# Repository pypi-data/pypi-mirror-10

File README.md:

# PyPI code 10

This repository is part of a project to make all code in PyPI as accessible as possible. For more information 
on the project and to find out how to utilise this data, see the website: https://py-code.org/

This repo contains 40000 packages uploaded to PyPI between 
2015-04-15 19:18 and 2015-07-14 03:23.

The repo is 99% (39941/40000) complete.

Package contents can be found [in the code branch](https://github.com/pypi-data/pypi-mirror-10/tree/code/packages).

A browsable package list for all repositories [all packages here](https://py-code.org/repositories/pypi-mirror-10).

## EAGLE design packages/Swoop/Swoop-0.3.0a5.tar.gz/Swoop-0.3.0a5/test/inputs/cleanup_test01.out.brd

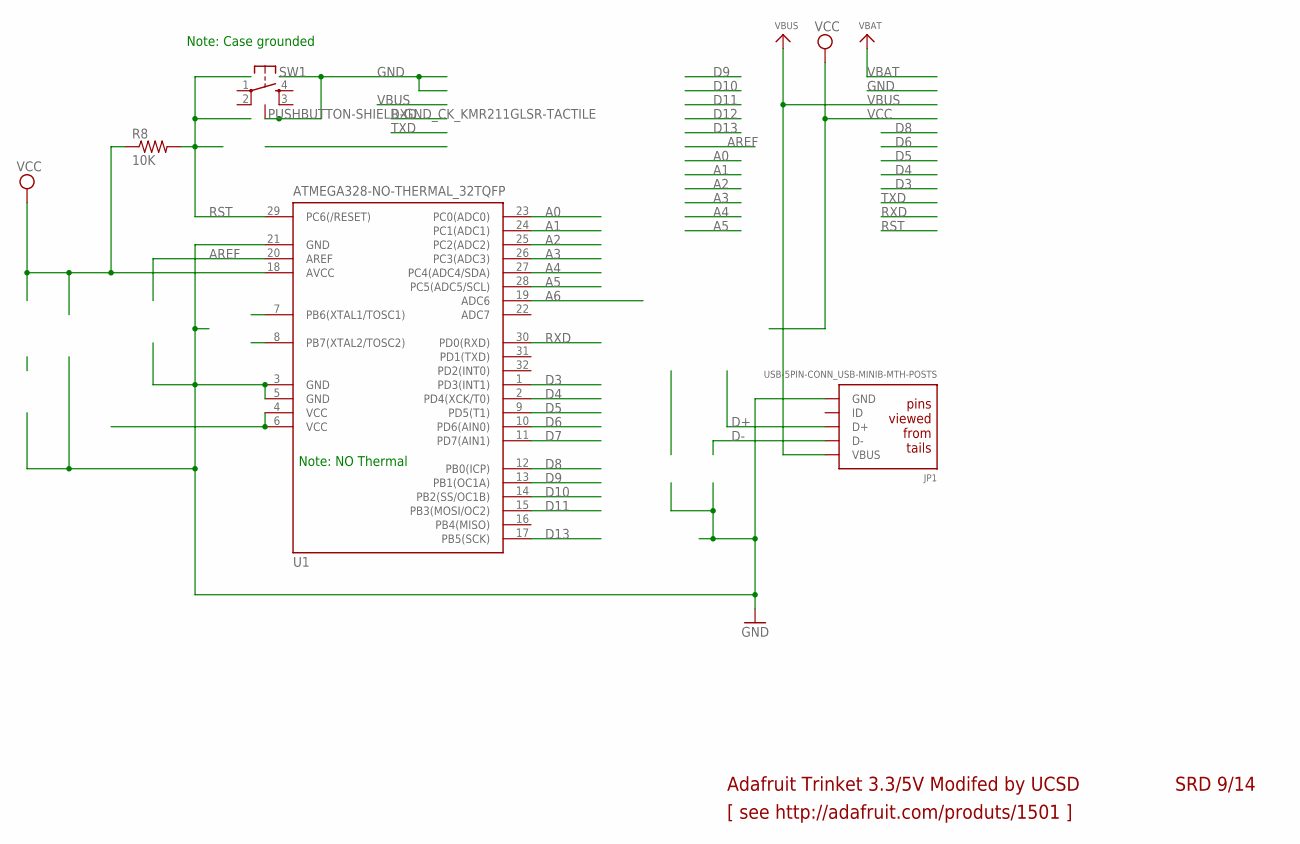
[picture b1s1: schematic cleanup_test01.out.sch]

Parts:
JP1: USB-5PIN-CONN_USB-MINIB-MTH-POSTS; FCI_10033526; MPN 10033526-N3212MLF
SW1: PUSHBUTTON-SHIELD-GND_CK_KMR211GLSR-TACTILE; CK_KMR211GLSR; MPN KMR211GLFS
U1: ATMEGA328-NO-THERMAL_32TQFP; QFP80P900X900X120-32L30HS; MPN ATMEGA328-AU

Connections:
A0: U1.23 (PC0(ADC0))
A1: U1.24 (PC1(ADC1))
A2: U1.25 (PC2(ADC2))
A3: U1.26 (PC3(ADC3))
A4: U1.27 (PC4(ADC4/SDA))
A5: U1.28 (PC5(ADC5/SCL))
A6: U1.19 (ADC6)
AREF: U1.20 (AREF)
D3: U1.1 (PD3(INT1))
D4: U1.2 (PD4(XCK/T0))
D5: U1.9 (PD5(T1))
D6: U1.10 (PD6(AIN0))
D7: U1.11 (PD7(AIN1))
D8: U1.12 (PB0(ICP))
D9: U1.13 (PB1(OC1A))
D10: U1.14 (PB2(SS/OC1B))
D11: U1.15 (PB3(MOSI/OC2))
D13: U1.17 (PB5(SCK))
D+: JP1.3 (D+)
D-: JP1.2 (D-)
GND: JP1.5 (GND), SW1.1, SW1.4, SW1.5, U1.3 (GND), U1.5 (GND), U1.21 (GND)
unnamed: U1.4 (VCC), U1.6 (VCC)
RST: SW1.2, SW1.3, U1.29 (PC6(/RESET))
RXD: U1.30 (PD0(RXD))
VBUS: JP1.1 (VBUS)
VCC: U1.18 (AVCC)

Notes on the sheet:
[ see http://adafruit.com/produts/1501 ]
Adafruit Trinket 3.3/5V Modifed by UCSD
SRD 9/14
Note: Case grounded
Note: NO Thermal

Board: 2 copper layers, 3 parts (0 on the bottom side), 3 nets, no tracks yet.

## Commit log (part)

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2023-08-06 Add package airship-icloud/1.4.6/airship_icloud-1.4.6-py2.py3-none-any.whl
2023-08-06 Add package fontaine/1.3.2/fontaine-1.3.2.tar.gz
2023-08-06 Add package coala/0.1.1.dev1694/coala-0.1.1.dev1694.tar.gz
2023-08-06 Add package phconvert/0.6.2/phconvert-0.6.2-py2.py3-none-any.whl
2023-08-06 Add package coala/0.1.1.dev1695/coala-0.1.1.dev1695.tar.gz
2023-08-06 Add package planetary_test_data/0.3.0/planetary_test_data-0.3.0.tar.gz
2023-08-06 Add package django-post-office/2.0.0/django-post_office-2.0.0.tar.gz
2023-08-06 Add package PySMT/0.4.1/PySMT-0.4.1.tar.gz
2023-08-06 Add package processout/1.2.0/processout-1.2.0.tar.gz
2023-08-06 Add package ipaddress/1.0.11/ipaddress-1.0.11-py27-none-any.whl
2023-08-06 Add package ftw.testbrowser/1.16.1/ftw.testbrowser-1.16.1.tar.gz
2023-08-06 Add package ipaddress/1.0.11/ipaddress-1.0.11.tar.gz
2023-08-06 Add package jmbo-sitemap/2.0.1/jmbo-sitemap-2.0.1.tar.gz
2023-08-06 Add package pyTelegramBotAPI/0.2.3/pyTelegramBotAPI-0.2.3.tar.gz
2023-08-06 Add package gocardless-pro/0.1.2/gocardless_pro-0.1.2.tar.gz
2023-08-06 Add package muffin/0.0.95/muffin-0.0.95-py2.py3-none-any.whl
2023-08-06 Add package pytest-splinter/1.4.6/pytest-splinter-1.4.6.tar.gz
2023-08-06 Add package frojd-fabric/1.1.1/frojd-fabric-1.1.1.tar.gz
2023-08-06 Add package aTXT/1.0.5.7/aTXT-1.0.5.7.tar.gz
2023-08-06 Add package pyshark/0.3.6/pyshark-0.3.6.tar.gz
2023-08-06 Add package consular/0.1.0/consular-0.1.0.tar.gz
2023-08-06 Add package git-gifi/0.5/git_gifi-0.5-py2.7.egg
2023-08-06 Add package django-reversion-compare/0.5.3/django_reversion_compare-0.5.3-py2.py3-none-any.whl
2023-08-06 Add package git-gifi/0.5/git-gifi-0.5.tar.gz
2023-08-06 Add package DeCAF/0.1.0/DeCAF-0.1.0-py2.7.egg
2023-08-06 Add package vdf/1.9/vdf-1.9-py2.py3-none-any.whl
2023-08-06 Add package neoppod/1.4.0/neoppod-1.4.0.tar.gz
2023-08-06 Add package consular/0.2.0/consular-0.2.0.tar.gz
2023-08-06 Add package git-gifi/0.6/git-gifi-0.6.tar.gz
2023-08-06 Add package cornet/0.1.3/cornet-0.1.3.tar.gz
2023-08-06 Add package hestia-api/0.0.2/hestia-api-0.0.2.tar.gz
2023-08-06 Add package stups-senza/0.63/stups-senza-0.63.tar.gz
2023-08-06 Add package git-gifi/0.6/git_gifi-0.6-py2.py3-none-any.whl
2023-08-06 Add package scan_list/1.0.0/scan_list-1.0.0.tar.gz
2023-08-06 Add package BucketCache/0.11.0/BucketCache-0.11.0.tar.gz
2023-08-06 Add package emzed/2.17.0/emzed-2.17.0.tar.gz
2023-08-06 Add package WooCommerce/1.0.1/WooCommerce-1.0.1.tar.gz
2023-08-06 Add package nimoy/0.7.1/nimoy-0.7.1.tar.gz
2023-08-06 Add package amo-validator/1.7.8/amo-validator-1.7.8.tar.gz
2023-08-06 Add package shutit/0.8.67/shutit-0.8.67.tar.gz
2023-08-06 Add package MySmile/0.7.0/mysmile-0.7.0.zip
2023-08-06 Add package oddt/0.1.2.1/oddt-0.1.2.1-py2.7.egg
2023-08-06 Add package amo-validator/1.7.8/amo_validator-1.7.8-py2-none-any.whl
2023-08-06 Add package carpentry-ci/0.2.35/carpentry-ci-0.2.35.tar.gz
2023-08-06 Add package FuncDesigner/0.5611/FuncDesigner-0.5611.tar.gz
2023-08-06 Add package onegov.core/0.4.8/onegov.core-0.4.8-py2-none-any.whl
2023-08-06 Add package v1syncrt/1.2.5/v1syncrt-1.2.5.zip
2023-08-06 Add package trytond/3.2.8/trytond-3.2.8.tar.gz
2023-08-06 Add package django-protector/0.3.4/django-protector-0.3.4.tar.gz
2023-08-06 Add package OBITools/1.1.21/OBITools-1.1.21.tar.gz
2023-08-06 Add package django-taggit/0.16.2/django_taggit-0.16.2-py2.py3-none-any.whl
2023-08-06 Add package tencentyun_cos/1.0.1/tencentyun_cos-1.0.1.tar.gz
2023-08-06 Add package trytond/3.6.2/trytond-3.6.2.tar.gz
2023-08-06 Add package tryton/3.6.2/tryton-3.6.2.tar.gz
2023-08-06 Add package codefights/0.1/codefights-0.1.tar.gz
2023-08-06 Add package Hitboxy/0.1.9/hitboxy-0.1.9.zip
2023-08-06 Add package agora/0.5.6/agora-0.5.6.zip
2023-08-06 Add package proteus/3.4.4/proteus-3.4.4.tar.gz
2023-08-06 Add package proteus/3.0.4/proteus-3.0.4.tar.gz
2023-08-06 Add package neso/3.6.1/neso-3.6.1.tar.gz
2023-08-06 Add package geojson/1.2.2/geojson-1.2.2.tar.gz
2023-08-06 Add package universal-portfolios/0.1.1/universal-portfolios-0.1.1.tar.gz
2023-08-06 Add package rejected/3.6.2/rejected-3.6.2.tar.gz
2023-08-06 Add package rejected/3.6.2/rejected-3.6.2-py2-none-any.whl
2023-08-06 Add package trytond-sale-extra/3.6.2/trytond_sale_extra-3.6.2.tar.gz
2023-08-06 Add package oslo.middleware/2.4.0/oslo.middleware-2.4.0.tar.gz
2023-08-06 Add package scan_list/1.1.0/scan_list-1.1.0.tar.gz
2023-08-06 Add package oslo.service/0.4.0/oslo.service-0.4.0-py2.py3-none-any.whl
2023-08-06 Add package drf-nested-decorator/0.3/drf-nested-decorator-0.3.tar.gz
2023-08-06 Add package pypsh/0.7.3/pypsh-0.7.3.tar.gz
2023-08-06 Add package trytond-project-invoice/3.6.1/trytond_project_invoice-3.6.1.tar.gz
2023-08-06 Add package enhydris/0.5.1/enhydris-0.5.1.tar.gz
2023-08-06 Add package django-healthchecks/0.1.2/django-healthchecks-0.1.2.tar.gz
2023-08-06 Add package onegov.core/0.4.9/onegov.core-0.4.9-py2-none-any.whl
2023-08-06 Add package oslo.messaging/1.17.0/oslo.messaging-1.17.0.tar.gz
2023-08-06 Add package sfc/0.1.355/sfc-0.1.355.tar.gz
2023-08-06 Add package mongo-pool/0.4.1/mongo-pool-0.4.1.tar.gz
2023-08-06 Add package taskflow/1.15.0/taskflow-1.15.0-py2.py3-none-any.whl
2023-08-06 Add package whtc.recipe.configmanager/1.1.1/whtc.recipe.configmanager-1.1.1.tar.gz
2023-08-06 Add package trytond-product/3.6.1/trytond_product-3.6.1.tar.gz
2023-08-06 Add package moto/0.4.5/moto-0.4.5-py2.py3-none-any.whl
2023-08-06 Add package rpforest/1.1/rpforest-1.1.tar.gz
2023-08-06 Add package oslo.cache/0.3.0/oslo.cache-0.3.0-py2.py3-none-any.whl
2023-08-06 Add package django-healthchecks/0.1.2/django_healthchecks-0.1.2-py2-none-any.whl
2023-08-06 Add package django-happenings/0.2.6/django-happenings-0.2.6.tar.gz
2023-08-06 Add package oslo.cache/0.3.0/oslo.cache-0.3.0.tar.gz
2023-08-06 Add package hyperloglogs/0.1/hyperloglogs-0.1.tar.gz
2023-08-06 Add package trytond-product/3.0.2/trytond_product-3.0.2.tar.gz
2023-08-06 Add package django-calendarium/1.3/django-calendarium-1.3.tar.gz
2023-08-06 Add package TMDAng/1.0.0/TMDAng-1.0.0.zip
2023-08-06 Add package pytest-services/1.0.6/pytest-services-1.0.6.tar.gz
2023-08-06 Add package trytond-party/3.6.1/trytond_party-3.6.1.tar.gz
2023-08-06 Add package checkbox-support/0.20/checkbox-support-0.20.tar.gz
2023-08-06 Add package horizon_overrides_plugin/0.0.2/horizon_overrides_plugin-0.0.2.tar.gz
2023-08-06 Add package coala/0.1.1.dev1720/coala-0.1.1.dev1720.tar.gz
2023-08-06 Add package django-redis-cache/1.1.1/django-redis-cache-1.1.1.tar.gz
2023-08-06 Add package pyramid-wtforms/2.1.0/pyramid_wtforms-2.1.0.tar.gz
2023-08-06 Add package django-rest-framework-braces/0.1.4/django-rest-framework-braces-0.1.4.tar.gz
2023-08-06 Add package cybak/0.1.0/cybak-0.1.0.tar.gz
2023-08-06 Add package django-tribe-client/1.0.1/django-tribe-client-1.0.1.tar.gz
2023-08-06 Add package drf-tools/0.9.13/drf-tools-0.9.13.tar.gz
2023-08-06 Add package TMDAng/1.0.0/TMDAng-1.0.0-py3-none-any.whl
2023-08-06 Add package cybak/0.2.0/cybak-0.2.0.tar.gz
2023-08-06 Add package msmtools/1.0.1/msmtools-1.0.1.tar.gz
2023-08-06 Add package pyramid_pages/0.0.3/pyramid_pages-0.0.3.tar.gz
2023-08-06 Add package config-handle/0.1.0/config-handle-0.1.0.tar.gz
2023-08-06 Add package mozregression/0.37/mozregression-0.37.tar.gz
2023-08-06 Add package trytond-account-deposit/3.6.1/trytond_account_deposit-3.6.1.tar.gz
2023-08-06 Add package trytond-account-asset/3.6.1/trytond_account_asset-3.6.1.tar.gz
2023-08-06 Add package modish/0.1.0/modish-0.1.0.tar.gz
2023-08-06 Add package trytond-account-asset/3.2.4/trytond_account_asset-3.2.4.tar.gz
2023-08-06 Add package container-transform/0.6.0/container-transform-0.6.0.tar.gz
2023-08-06 Add package mixbox/0.0.9/mixbox-0.0.9.tar.gz
2023-08-06 Add package container-transform/0.6.0/container_transform-0.6.0-py2.py3-none-any.whl
2023-08-06 Add package sprockets.mixins.sentry/0.3.0/sprockets.mixins.sentry-0.3.0-py2.py3-none-any.whl
2023-08-06 Add package django-frontend/1.7.0/django_frontend-1.7.0-py2.py3-none-any.whl
2023-08-06 Add package coala/0.1.1.dev1737/coala-0.1.1.dev1737.tar.gz
2023-08-06 Add package pywinauto/0.5.1/pywinauto-0.5.1.zip
2023-08-06 Add package nkit4py/2.3.1/nkit4py-2.3.1.zip
2023-08-06 Add package LogToPG/0.1.1/LogToPG-0.1.1.tar.gz
2023-08-06 Add package tdl/1.5.0/tdl-1.5.0-py2.py3-none-any.whl
2023-08-06 Add package gaeforms/0.19/gaeforms-0.19.tar.gz
2023-08-06 Add package libtcod-cffi/0.2.3/libtcod_cffi-0.2.3-cp34-none-win32.whl
2023-08-06 Add package libtcod-cffi/0.2.3/libtcod-cffi-0.2.3.zip
2023-08-06 Add package eelbrain/0.17.1/eelbrain-0.17.1-py2.7-macosx-10.5-x86_64.egg
2023-08-06 Add package eelbrain/0.17.1/eelbrain-0.17.1-cp27-none-macosx_10_5_x86_64.whl
2023-08-06 Add package raven/5.4.4/raven-5.4.4.tar.gz
2023-08-06 Add package raven/5.4.4/raven-5.4.4-py2.py3-none-any.whl
2023-08-06 Add package hestia-api/0.0.4/hestia-api-0.0.4.tar.gz
2023-08-06 Add package mongolia/0.3.10/mongolia-0.3.10.tar.gz
2023-08-06 Add package hestia-api/0.0.3/hestia-api-0.0.3.tar.gz
2023-08-06 Add package flanker/0.4.33/flanker-0.4.33.tar.gz
2023-08-06 Add package pydendroheatmap/1.0.3/pydendroheatmap-1.0.3.tar.gz
2023-08-06 Add package stomp.py/4.1.2/stomp.py-4.1.2.tar.gz
2023-08-06 Add package pydendroheatmap/1.0.2/pydendroheatmap-1.0.2.tar.gz
2023-08-06 Add package bravado-core/2.0.0/bravado-core-2.0.0.tar.gz
2023-08-06 Add package frida/4.2.10/frida-4.2.10-py2.7-linux-x86_64.egg
2023-08-06 Add package python-jenkins/0.4.8/python_jenkins-0.4.8-py2-none-any.whl
2023-08-06 Add package hestia-api/0.0.5/hestia-api-0.0.5.tar.gz
2023-08-06 Add package Products.PloneFormGen/1.8.0.beta1/Products.PloneFormGen-1.8.0.beta1.zip
2023-08-06 Add package pydvdid/1.0/pydvdid-1.0.tar.gz
2023-08-06 Add package kombine/0.5.0/kombine-0.5.0.tar.gz
2023-08-06 Add package frida/4.2.10/frida-4.2.10-py3.4-linux-i686.egg
2023-08-06 Add package planetary_test_data/0.3.1/planetary_test_data-0.3.1-py2.py3-none-any.whl
2023-08-06 Add package pytest-services/1.0.7/pytest-services-1.0.7.tar.gz
2023-08-06 Add package vr.builder/1.1/vr.builder-1.1.tar.gz
2023-08-06 Add package tchannel/0.10.3/tchannel-0.10.3.tar.gz
2023-08-06 Add package NetStorageKit/1.0.8/NetStorageKit-1.0.8-py2-none-any.whl
2023-08-06 Add package tchannel/0.10.3/tchannel-0.10.3-py2-none-any.whl
2023-08-06 Add package planetary_test_data/0.3.1/planetary_test_data-0.3.1.tar.gz
2023-08-06 Add package radical.pilot/0.34/radical.pilot-0.34.tar.gz
2023-08-06 Add package SLACtrac/1.0.1/SLACtrac-1.0.1.tar.gz
2023-08-06 Add package mock/1.1.3/mock-1.1.3.tar.gz
2023-08-06 Add package queuetools/1.2/queuetools-1.2-py2.7.egg
2023-08-06 Add package mac/0.9.1/mac-0.9.1.tar.gz
2023-08-06 Add package SLACtrac/1.0.1/SLACtrac-1.0.1-py3-none-any.whl
2023-08-06 Add package watermarker-cli/0.0.1/watermarker-cli-0.0.1.zip
2023-08-06 Add package rookout/0.4.3/rookout-0.4.3.tar.gz
2023-08-06 Add package wagtail-blog/1.4.7/wagtail-blog-1.4.7.tar.gz
2023-08-06 Add package majestic-components/7.0/majestic-components-7.0.zip
2023-08-06 Add package frida/4.2.10/frida-4.2.10-py2.6-macosx-10.10-intel.egg
2023-08-06 Add package frida/4.2.10/frida-4.2.10-py3.4-win-amd64.egg
2023-08-06 Add package pyinter/0.1.8/pyinter-0.1.8.tar.gz
2023-08-06 Add package eemeter/0.1.7/eemeter-0.1.7-py2.py3-none-any.whl
2023-08-06 Add package nilearn/0.1.4.post1/nilearn-0.1.4.post1.tar.gz
2023-08-06 Add package nilearn/0.1.4.post1/nilearn-0.1.4.post1-py2.7.egg
2023-08-06 Add package nilearn/0.1.4.post1/nilearn-0.1.4.post1-py2.py3-none-any.whl
2023-08-06 Add package eemeter/0.1.8/eemeter-0.1.8-py2.py3-none-any.whl
2023-08-06 Add package djangofloor/0.13.5/djangofloor-0.13.5.tar.gz
2023-08-06 Add package eemeter/0.1.8/eemeter-0.1.8.tar.gz
2023-08-06 Add package comiccrawler/2015.7.14/comiccrawler-2015.7.14.zip
2023-08-06 Add package pyDOE/0.3.8/pyDOE-0.3.8.zip
2023-08-06 Add package django-vinaigrette/0.5.0/django-vinaigrette-0.5.0.tar.gz
2023-08-06 Add package frida/4.2.10/frida-4.2.10-py2.7-macosx-10.8-intel.egg
2023-08-06 Add package frida/4.2.10/frida-4.2.10-py3.4-macosx-10.6-intel.egg
2023-08-06 Add package frida/4.2.10/frida-4.2.10-py2.7-macosx-10.10-intel.egg
2023-10-16 Add package ftcbz/2.1.0/ftcbz-2.1.0-py3.4.egg

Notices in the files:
parts and their libraries:
microbuilder: This work is placed in the public domain, and may be freely used for commercial and non-commercial work with the following conditions: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
